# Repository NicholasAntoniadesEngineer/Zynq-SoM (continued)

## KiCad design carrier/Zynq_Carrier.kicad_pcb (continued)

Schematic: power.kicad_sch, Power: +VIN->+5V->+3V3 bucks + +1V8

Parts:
C20001, C20004, C20007, C20009, C20025, C20029: 100n; C_0603_1608Metric; LCSC C14663
C20002, C20003: 10u; C_1206_3216Metric; LCSC C13585
C20005, C20006, C20008, C20010, C20011, C20026, C20030: 22u; C_0805_2012Metric; LCSC C45783
C20012, C20013, C20024, C20028, C20031, C20032: 1u; C_0603_1608Metric; LCSC C15849
C20023, C20027: 22p; C_0603_1608Metric; LCSC C1653
D20001, D20002, D20003: red; LED_0603_1608Metric; LCSC C2286
L20001, L20002: 10uH; SWPA8040S100MT; LCSC C37429
Q20001: AO3400A; SOT-23; MPN AO3400A; LCSC C20917
R20001: 40.2k; R_0603_1608Metric; LCSC C12447
R20002, R20005: 10k; R_0603_1608Metric; LCSC C25804
R20003, R20007, R20012, R20015: 1k; R_0603_1608Metric; LCSC C21190
R20004: 23.2k; R_0603_1608Metric; LCSC C23346
R20006, R20009: 330R; R_0603_1608Metric; LCSC C23138
R20008: 100k; R_0603_1608Metric; LCSC C25803
R20010, R20014: 22k; R_0603_1608Metric; LCSC C31850
R20011, R20013: 10R; R_0603_1608Metric; LCSC C22859
TP20001: +5V; TestPoint_Pad_D1.5mm
TP20002: +3V3; TestPoint_Pad_D1.5mm
TP20003: +1V8; TestPoint_Pad_D1.5mm
TP20004: GND; TestPoint_Pad_D1.5mm
U20001, U20002: LM61460AANRJRR; LCSC C2864505
U20003: AP2112K-1.8; SOT-23-5; MPN AP2112K-1.8TRG1; LCSC C176944

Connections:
+1V8: R20007.1, TP20003.1; also elsewhere on the board
+1V8_REG: C20013.1, U20003.5 (VOUT); also elsewhere on the board
+3V3: C20012.1, D20003.2 (A), TP20002.1, U20003.1 (VIN); also elsewhere on the board
+3V3_REG: C20010.1, C20011.1, C20023.1, D20002.2 (A), L20002.2, R20004.1, R20013.1; also elsewhere on the board
+5V: C20007.1, C20008.1, C20029.1, C20030.1, TP20001.1, U20002.8 (VIN1), U20002.12 (VIN2); also elsewhere on the board
+5V_REG: C20005.1, C20006.1, C20026.1, C20027.1, D20001.2 (A), L20001.2, R20001.1, R20011.1; also elsewhere on the board
+VIN_SYS: C20001.1, C20002.1, C20003.1, C20025.1, U20001.8 (VIN1), U20001.12 (VIN2); also elsewhere on the board
/power/BIAS_3V3: C20032.1, R20013.2, U20002.1 (BIAS)
/power/BIAS_5V0: C20028.1, R20011.2, U20001.1 (BIAS)
/power/RT_3V3: R20014.1, U20002.6 (RT)
/power/RT_5V0: R20010.1, U20001.6 (RT)
EN_1V8: U20003.3 (EN); also elsewhere on the board
EN_3V3: U20002.7 (EN/SYNC); also elsewhere on the board
EN_5V0: U20001.7 (EN/SYNC); also elsewhere on the board
GND: C20001.2, C20002.2, C20003.2, C20005.2, C20006.2, C20007.2, C20008.2, C20010.2, C20011.2, C20012.2, C20013.2, C20024.2, C20025.2, C20026.2, C20028.2, C20029.2, C20030.2, C20031.2, C20032.2, Q20001.2 (S), R20002.2, R20003.2, R20005.2, R20006.2, R20008.2, R20010.2, R20014.2, TP20004.1, U20001.3 (AGND), U20001.9 (PGND1), U20001.11 (PGND2), U20002.3 (AGND), U20002.9 (PGND1), U20002.11 (PGND2), U20003.2 (GND); also elsewhere on the board
unnamed: C20023.2, R20015.1
unnamed: C20027.2, R20012.1
unnamed: D20001.1 (K), R20003.1
unnamed: D20002.1 (K), R20006.1
unnamed: D20003.1 (K), R20009.1
unnamed: Q20001.3 (D), R20009.2
unnamed: Q20001.1 (G), R20007.2, R20008.1
unnamed: C20004.1, U20001.13 (RBOOT), U20001.14 (CBOOT)
unnamed: R20001.2, R20002.1, R20012.2, U20001.4 (FB)
unnamed: C20004.2, L20001.1, U20001.10 (SW)
unnamed: C20024.1, U20001.2 (VCC)
unnamed: C20009.1, U20002.13 (RBOOT), U20002.14 (CBOOT)
unnamed: R20004.2, R20005.1, R20015.2, U20002.4 (FB)
unnamed: C20009.2, L20002.1, U20002.10 (SW)
unnamed: C20031.1, U20002.2 (VCC)

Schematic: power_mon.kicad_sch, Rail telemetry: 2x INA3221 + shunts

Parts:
C21001, C21002: 100n; C_0603_1608Metric; LCSC C14663
C21003: 10u; C_0805_2012Metric; LCSC C15850
R21001: 10k; R_0603_1608Metric; LCSC C25804
RS21001, RS21002, RS21003: 10mR; RLM12FTCMR010; LCSC C188070
RS21004: 20mR; RLM12FTCMR020; LCSC C393094
U21001, U21002: INA3221AIRGVR; LCSC C181255

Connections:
+1V8: RS21004.2, U21002.11 (IN-1); also elsewhere on the board
+1V8_REG: RS21004.1, U21002.12 (IN+1); also elsewhere on the board
+3V3: RS21003.2, U21001.1 (IN-3); also elsewhere on the board
+3V3_REG: RS21003.1, U21001.2 (IN+3); also elsewhere on the board
+3V3_SC: C21001.1, C21002.1, C21003.1, R21001.1, U21001.4 (VS), U21001.16 (VPU), U21002.4 (VS), U21002.5 (A0), U21002.16 (VPU); also elsewhere on the board
+5V: RS21002.2, U21001.14 (IN-2); also elsewhere on the board
+5V_REG: RS21002.1, U21001.15 (IN+2); also elsewhere on the board
+VIN: RS21001.1, U21001.12 (IN+1); also elsewhere on the board
+VIN_SYS: RS21001.2, U21001.11 (IN-1); also elsewhere on the board
GND: C21001.2, C21002.2, C21003.2, U21001.3 (GND), U21001.5 (A0), U21001.17 (PAD), U21002.1 (IN-3), U21002.2 (IN+3), U21002.3 (GND), U21002.14 (IN-2), U21002.15 (IN+2), U21002.17 (PAD); also elsewhere on the board
PMON_ALERT_N: R21001.2, U21001.9 (CRITICAL), U21002.9 (CRITICAL); also elsewhere on the board
STM32_I2C2_SCL: U21001.6 (SCL), U21002.6 (SCL); also elsewhere on the board
STM32_I2C2_SDA: U21001.7 (SDA), U21002.7 (SDA); also elsewhere on the board

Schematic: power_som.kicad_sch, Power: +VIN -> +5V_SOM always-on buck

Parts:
C22014, C22017, C22025: 100n; C_0603_1608Metric; LCSC C14663
C22015, C22016: 10u; C_1206_3216Metric; LCSC C13585
C22018, C22019: 22u; C_0805_2012Metric; LCSC C45783
C22021: 22p; C_0603_1608Metric; LCSC C1653
C22022, C22023: 1u; C_0603_1608Metric; LCSC C15849
D22004: red; LED_0603_1608Metric; LCSC C2286
L22003: 10uH; SWPA8040S100MT; LCSC C37429
R22014: 47.5k; R_0603_1608Metric; LCSC C23061
R22015: 13k; R_0603_1608Metric; LCSC C22797
R22016, R22019: 1k; R_0603_1608Metric; LCSC C21190
R22017: 10R; R_0603_1608Metric; LCSC C22859
R22018: 22k; R_0603_1608Metric; LCSC C31850
TP22001: +5V_SOM; TestPoint_Pad_D1.5mm
U22004: LM61460AANRJRR; LCSC C2864505

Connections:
+5V_SOM: C22018.1, C22019.1, C22021.1, D22004.2 (A), L22003.2, R22014.1, R22017.1, TP22001.1; also elsewhere on the board
+VIN_SYS: C22014.1, C22015.1, C22016.1, C22025.1, U22004.7 (EN/SYNC), U22004.8 (VIN1), U22004.12 (VIN2); also elsewhere on the board
/power_som/BIAS_5V_SOM: C22023.1, R22017.2, U22004.1 (BIAS)
/power_som/RT_5V_SOM: R22018.1, U22004.6 (RT)
GND: C22014.2, C22015.2, C22016.2, C22018.2, C22019.2, C22022.2, C22023.2, C22025.2, R22015.2, R22016.2, R22018.2, U22004.3 (AGND), U22004.9 (PGND1), U22004.11 (PGND2); also elsewhere on the board
unnamed: C22021.2, R22019.1
unnamed: D22004.1 (K), R22016.1
unnamed: C22017.1, U22004.13 (RBOOT), U22004.14 (CBOOT)
unnamed: R22014.2, R22015.1, R22019.2, U22004.4 (FB)
unnamed: C22017.2, L22003.1, U22004.10 (SW)
unnamed: C22022.1, U22004.2 (VCC)

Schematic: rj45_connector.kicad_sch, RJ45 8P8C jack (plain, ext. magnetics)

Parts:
J23001: KH-5224-8P8C-D; LCSC C2828085
R23001, R23002: 330R; R_0603_1608Metric; LCSC C23138

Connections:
+3V3: R23001.1, R23002.1; also elsewhere on the board
CHASSIS_GND: J23001.13 (SHELL); also elsewhere on the board
ETH_LINE_MDI_0_N: J23001.2; also elsewhere on the board
ETH_LINE_MDI_0_P: J23001.1; also elsewhere on the board
ETH_LINE_MDI_1_N: J23001.6; also elsewhere on the board
ETH_LINE_MDI_1_P: J23001.3; also elsewhere on the board
ETH_LINE_MDI_2_N: J23001.5; also elsewhere on the board
ETH_LINE_MDI_2_P: J23001.4; also elsewhere on the board
ETH_LINE_MDI_3_N: J23001.8; also elsewhere on the board
ETH_LINE_MDI_3_P: J23001.7; also elsewhere on the board
GND: J23001.10 (LED-L-), J23001.12 (LED-R-); also elsewhere on the board
unnamed: J23001.9 (LED-L+), R23001.2
unnamed: J23001.11 (LED-R+), R23002.2

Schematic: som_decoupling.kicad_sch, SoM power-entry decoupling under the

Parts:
C35001, C35002, C35007, C35008, C35013, C35014: 22u; C_0805_2012Metric; LCSC C45783
C35003, C35004, C35005, C35006, C35009, C35010, C35011, C35012, C35015, C35016, C35017, C35018: 100n; C_0603_1608Metric; LCSC C14663

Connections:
+3V3: C35007.1, C35008.1, C35009.1, C35010.1, C35011.1, C35012.1; also elsewhere on the board
+3V3_SC: C35013.1, C35014.1, C35015.1, C35016.1, C35017.1, C35018.1; also elsewhere on the board
+5V_SOM: C35001.1, C35002.1, C35003.1, C35004.1, C35005.1, C35006.1; also elsewhere on the board
GND: C35001.2, C35002.2, C35003.2, C35004.2, C35005.2, C35006.2, C35007.2, C35008.2, C35009.2, C35010.2, C35011.2, C35012.2, C35013.2, C35014.2, C35015.2, C35016.2, C35017.2, C35018.2; also elsewhere on the board

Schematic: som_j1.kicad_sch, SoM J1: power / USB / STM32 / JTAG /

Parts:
J24001: DF40C-100DP-0.4V(51); DF40C-100DP-0.4V_51; LCSC C531031

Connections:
+3V3_SC: J24001.37; also elsewhere on the board
+5V_SOM: J24001.1, J24001.2, J24001.3, J24001.4, J24001.5, J24001.6, J24001.7, J24001.8, J24001.9, J24001.10, J24001.11, J24001.12, J24001.13, J24001.14; also elsewhere on the board
ETH_LED1: J24001.98
ETH_LED2: J24001.94
ETH_PHY_MDI0_N: J24001.95; also elsewhere on the board
ETH_PHY_MDI0_P: J24001.97; also elsewhere on the board
ETH_PHY_MDI1_N: J24001.89; also elsewhere on the board
ETH_PHY_MDI1_P: J24001.91; also elsewhere on the board
ETH_PHY_MDI2_N: J24001.83; also elsewhere on the board
ETH_PHY_MDI2_P: J24001.85; also elsewhere on the board
ETH_PHY_MDI3_N: J24001.77; also elsewhere on the board
ETH_PHY_MDI3_P: J24001.79; also elsewhere on the board
FMC_LA08_N: J24001.92; also elsewhere on the board
FMC_LA08_P: J24001.74; also elsewhere on the board
FMC_LA09_N: J24001.84; also elsewhere on the board
FMC_LA09_P: J24001.80; also elsewhere on the board
FMC_LA10_N: J24001.88; also elsewhere on the board
FMC_LA10_P: J24001.90; also elsewhere on the board
FMC_LA11_N: J24001.76; also elsewhere on the board
FMC_LA11_P: J24001.78; also elsewhere on the board
GND: J24001.15, J24001.16, J24001.17, J24001.18, J24001.23, J24001.28, J24001.34, J24001.39, J24001.44, J24001.51, J24001.62, J24001.63, J24001.72, J24001.75, J24001.81, J24001.82, J24001.87, J24001.93, J24001.96, J24001.99; also elsewhere on the board
IO_0_35: J24001.86
IO_L2_N_35: J24001.100
SC_INT_N: J24001.41; also elsewhere on the board
SDIO_CLK: J24001.67; also elsewhere on the board
SDIO_CMD: J24001.69; also elsewhere on the board
SDIO_D0: J24001.65; also elsewhere on the board
SDIO_D1: J24001.61; also elsewhere on the board
SDIO_D2: J24001.73; also elsewhere on the board
SDIO_D3: J24001.71; also elsewhere on the board
STM32_BOOT0: J24001.57; also elsewhere on the board
STM32_GPIO5: J24001.53; also elsewhere on the board
STM32_GPIO6: J24001.45; also elsewhere on the board
STM32_GPIO7: J24001.59; also elsewhere on the board
STM32_GPIO8: J24001.54; also elsewhere on the board
STM32_I2C2_SCL: J24001.55; also elsewhere on the board
STM32_I2C2_SDA: J24001.49; also elsewhere on the board
STM32_NRST: J24001.47; also elsewhere on the board
STM32_RAIL_EN_1V8: J24001.43; also elsewhere on the board
STM32_RAIL_EN_3V3: J24001.35; also elsewhere on the board
STM32_RAIL_EN_5V0: J24001.33; also elsewhere on the board
STM32_USB_CC1: J24001.29; also elsewhere on the board
STM32_USB_CC2: J24001.31; also elsewhere on the board
STM32_USB_D_N: J24001.21; also elsewhere on the board
STM32_USB_D_P: J24001.19; also elsewhere on the board
USB_D+: J24001.32; also elsewhere on the board
USB_D-: J24001.30; also elsewhere on the board
USB_ID: J24001.20; also elsewhere on the board
USB_VBUS: J24001.22; also elsewhere on the board
VBUS_OUT_EN: J24001.38; also elsewhere on the board
ZYNQ_PS_MIO0: J24001.50
ZYNQ_PS_MIO7/VM0: J24001.40
ZYNQ_PS_MIO8\VM1: J24001.36
ZYNQ_PS_MIO9: J24001.52
ZYNQ_PS_MIO12: J24001.46
ZYNQ_PS_UART0_RXD: J24001.42; also elsewhere on the board
ZYNQ_PS_UART0_TXD: J24001.48; also elsewhere on the board
ZYNQ_TCK: J24001.64; also elsewhere on the board
ZYNQ_TDI: J24001.70; also elsewhere on the board
ZYNQ_TDO: J24001.68; also elsewhere on the board
ZYNQ_TMS: J24001.66; also elsewhere on the board

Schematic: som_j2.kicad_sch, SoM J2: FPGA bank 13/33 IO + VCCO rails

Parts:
J25002: DF40C-100DP-0.4V(51); DF40C-100DP-0.4V_51; LCSC C531031

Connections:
+3V3: J25002.1, J25002.2, J25002.3, J25002.98, J25002.99, J25002.100; also elsewhere on the board
DBG_UART_RXD: J25002.42; also elsewhere on the board
DBG_UART_TXD: J25002.40; also elsewhere on the board
ESC_BUF_OE_N: J25002.57; also elsewhere on the board
ESC_FAULT_N: J25002.37; also elsewhere on the board
ESC_PWM_IN0: J25002.81; also elsewhere on the board
ESC_PWM_IN1: J25002.83; also elsewhere on the board
ESC_PWM_IN2: J25002.93; also elsewhere on the board
ESC_PWM_IN3: J25002.91; also elsewhere on the board
GND: J25002.4, J25002.5, J25002.6, J25002.15, J25002.16, J25002.25, J25002.26, J25002.35, J25002.36, J25002.45, J25002.46, J25002.55, J25002.56, J25002.65, J25002.66, J25002.75, J25002.76, J25002.85, J25002.86, J25002.95, J25002.96, J25002.97; also elsewhere on the board
HDMI_RX_5V_DET: J25002.44; also elsewhere on the board
HDMI_RX_CEC: J25002.59; also elsewhere on the board
HDMI_RX_CLK_N: J25002.88; also elsewhere on the board
HDMI_RX_CLK_P: J25002.90; also elsewhere on the board
HDMI_RX_D0_N: J25002.94; also elsewhere on the board
HDMI_RX_D0_P: J25002.92; also elsewhere on the board
HDMI_RX_D1_N: J25002.84; also elsewhere on the board
HDMI_RX_D1_P: J25002.82; also elsewhere on the board
HDMI_RX_D2_N: J25002.80; also elsewhere on the board
HDMI_RX_D2_P: J25002.78; also elsewhere on the board
IO_25_13: J25002.23; also elsewhere on the board
IO_L2_N_13: J25002.14; also elsewhere on the board
IO_L2_P_13: J25002.20; also elsewhere on the board
IO_L3_N_13: J25002.43; also elsewhere on the board
IO_L3_P_13: J25002.18; also elsewhere on the board
IO_L4_N_13: J25002.63; also elsewhere on the board
IO_L4_P_13: J25002.61; also elsewhere on the board
IO_L5P_13: J25002.38; also elsewhere on the board
IO_L5_N_13: J25002.24; also elsewhere on the board
IO_L6_P_13: J25002.21; also elsewhere on the board
IO_L6_P_33: J25002.89
IO_L7_N_13: J25002.64; also elsewhere on the board
IO_L7_P_13: J25002.62; also elsewhere on the board
IO_L8_N_13: J25002.60; also elsewhere on the board
IO_L8_P_13: J25002.58; also elsewhere on the board
IO_L9_DQS_N_13: J25002.48; also elsewhere on the board
IO_L9_DQS_P_13: J25002.50; also elsewhere on the board
IO_L10_N_13: J25002.51; also elsewhere on the board
IO_L10_P_13: J25002.53; also elsewhere on the board
IO_L15_P_13: J25002.9; also elsewhere on the board
IO_L19_P_13: J25002.12; also elsewhere on the board
IO_L21_P_13: J25002.13; also elsewhere on the board
IO_L22_P_13: J25002.19; also elsewhere on the board
IO_L24_N_13: J25002.7; also elsewhere on the board
IO_L24_P_13: J25002.10; also elsewhere on the board
LCD_CTP_INT: J25002.32; also elsewhere on the board
LCD_CTP_RST: J25002.34; also elsewhere on the board
LCD_CTP_SCL: J25002.28; also elsewhere on the board
LCD_CTP_SDA: J25002.30; also elsewhere on the board
PL_BTN0: J25002.79; also elsewhere on the board
PL_BTN1: J25002.87; also elsewhere on the board
PMODX_IO1: J25002.29; also elsewhere on the board
PMODX_IO2: J25002.27; also elsewhere on the board
PMODX_IO3: J25002.33; also elsewhere on the board
PMODX_IO4: J25002.31; also elsewhere on the board
PMODX_IO5: J25002.41; also elsewhere on the board
PMODX_IO6: J25002.39; also elsewhere on the board
PMODX_IO7: J25002.49; also elsewhere on the board
PMODX_IO8: J25002.47; also elsewhere on the board
SD_CARD_DETECT: J25002.17; also elsewhere on the board
ZYNQ_HDMI_TX_CEC: J25002.77; also elsewhere on the board
ZYNQ_HDMI_TX_HPD: J25002.54; also elsewhere on the board
ZYNQ_HDMI_TX_SCL: J25002.22; also elsewhere on the board
ZYNQ_HDMI_TX_SDA: J25002.52; also elsewhere on the board
ZYNQ_HDMI_TX_TMDS_0_N: J25002.69; also elsewhere on the board
ZYNQ_HDMI_TX_TMDS_0_P: J25002.67; also elsewhere on the board
ZYNQ_HDMI_TX_TMDS_1_N: J25002.68; also elsewhere on the board
ZYNQ_HDMI_TX_TMDS_1_P: J25002.70; also elsewhere on the board
ZYNQ_HDMI_TX_TMDS_2_N: J25002.74; also elsewhere on the board
ZYNQ_HDMI_TX_TMDS_2_P: J25002.72; also elsewhere on the board
ZYNQ_HDMI_TX_TMDS_CLK_N: J25002.73; also elsewhere on the board
ZYNQ_HDMI_TX_TMDS_CLK_P: J25002.71; also elsewhere on the board
ZYNQ_PS_UART0_CTS_N: J25002.11; also elsewhere on the board
ZYNQ_PS_UART0_RTS_N: J25002.8; also elsewhere on the board

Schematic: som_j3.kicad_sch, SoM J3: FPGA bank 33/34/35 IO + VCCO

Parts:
J26003: DF40C-100DP-0.4V(51); DF40C-100DP-0.4V_51; LCSC C531031

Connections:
+2V5_VADJ: J26003.1, J26003.2, J26003.4; also elsewhere on the board
+3V3: J26003.97, J26003.99; also elsewhere on the board
CAM_CLK_N: J26003.11; also elsewhere on the board
CAM_CLK_P: J26003.9; also elsewhere on the board
CAM_D0_N: J26003.7; also elsewhere on the board
CAM_D0_P: J26003.5; also elsewhere on the board
CAM_D1_N: J26003.15; also elsewhere on the board
CAM_D1_P: J26003.17; also elsewhere on the board
CAM_EN: J26003.85; also elsewhere on the board
CAM_LED: J26003.87; also elsewhere on the board
CAM_SCL: J26003.86; also elsewhere on the board
CAM_SDA: J26003.89; also elsewhere on the board
ESC_PWM_IN4: J26003.91; also elsewhere on the board
ESC_PWM_IN5: J26003.93; also elsewhere on the board
ESC_PWM_IN6: J26003.92; also elsewhere on the board
ESC_PWM_IN7: J26003.94; also elsewhere on the board
FMC_CLK0_M2C_N: J26003.16; also elsewhere on the board
FMC_CLK0_M2C_P: J26003.14; also elsewhere on the board
FMC_CLK1_M2C_N: J26003.10; also elsewhere on the board
FMC_CLK1_M2C_P: J26003.8; also elsewhere on the board
FMC_LA00_CC_N: J26003.20; also elsewhere on the board
FMC_LA00_CC_P: J26003.22; also elsewhere on the board
FMC_LA01_CC_N: J26003.26; also elsewhere on the board
FMC_LA01_CC_P: J26003.24; also elsewhere on the board
FMC_LA02_N: J26003.35; also elsewhere on the board
FMC_LA02_P: J26003.37; also elsewhere on the board
FMC_LA03_N: J26003.32; also elsewhere on the board
FMC_LA03_P: J26003.34; also elsewhere on the board
FMC_LA04_N: J26003.44; also elsewhere on the board
FMC_LA04_P: J26003.42; also elsewhere on the board
FMC_LA05_N: J26003.45; also elsewhere on the board
FMC_LA05_P: J26003.47; also elsewhere on the board
FMC_LA06_N: J26003.49; also elsewhere on the board
FMC_LA06_P: J26003.51; also elsewhere on the board
FMC_LA07_N: J26003.52; also elsewhere on the board
FMC_LA07_P: J26003.50; also elsewhere on the board
GND: J26003.3, J26003.6, J26003.12, J26003.13, J26003.18, J26003.23, J26003.28, J26003.33, J26003.38, J26003.43, J26003.48, J26003.53, J26003.58, J26003.63, J26003.68, J26003.73, J26003.80, J26003.83, J26003.90, J26003.95, J26003.100; also elsewhere on the board
IO_L16_N_35: J26003.29
IO_L16_P_35: J26003.31
IO_L18_N_35: J26003.25
IO_L18_P_35: J26003.27
IO_L22_N_34: J26003.84
IO_L23_P_34: J26003.88
IO_L24_P_34: J26003.82
LCD_B0: J26003.65; also elsewhere on the board
LCD_B1: J26003.66; also elsewhere on the board
LCD_B2: J26003.67; also elsewhere on the board
LCD_B3: J26003.69; also elsewhere on the board
LCD_B4: J26003.70; also elsewhere on the board
LCD_B5: J26003.71; also elsewhere on the board
LCD_B6: J26003.72; also elsewhere on the board
LCD_B7: J26003.74; also elsewhere on the board
LCD_BL_PWM: J26003.81; also elsewhere on the board
LCD_DE: J26003.78; also elsewhere on the board
LCD_DISP: J26003.79; also elsewhere on the board
LCD_G0: J26003.55; also elsewhere on the board
LCD_G1: J26003.56; also elsewhere on the board
LCD_G2: J26003.57; also elsewhere on the board
LCD_G3: J26003.59; also elsewhere on the board
LCD_G4: J26003.60; also elsewhere on the board
LCD_G5: J26003.61; also elsewhere on the board
LCD_G6: J26003.62; also elsewhere on the board
LCD_G7: J26003.64; also elsewhere on the board
LCD_HSYNC: J26003.76; also elsewhere on the board
LCD_PCLK: J26003.75; also elsewhere on the board
LCD_R0: J26003.19; also elsewhere on the board
LCD_R1: J26003.21; also elsewhere on the board
LCD_R2: J26003.30; also elsewhere on the board
LCD_R3: J26003.36; also elsewhere on the board
LCD_R4: J26003.40; also elsewhere on the board
LCD_R5: J26003.41; also elsewhere on the board
LCD_R6: J26003.46; also elsewhere on the board
LCD_R7: J26003.54; also elsewhere on the board
LCD_VSYNC: J26003.77; also elsewhere on the board
PUDC_34: J26003.39; also elsewhere on the board
WATCHDOG_KICK: J26003.96; also elsewhere on the board
WATCHDOG_RST_N: J26003.98; also elsewhere on the board

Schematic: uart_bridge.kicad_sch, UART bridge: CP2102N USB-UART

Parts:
C27001, C27003, C27004: 100n; C_0603_1608Metric; LCSC C14663
C27002: 10u; C_0805_2012Metric; LCSC C15850
R27001: 1k; R_0603_1608Metric; LCSC C21190
R27002: 22k1; R_0603_1608Metric; LCSC C25961
R27003: 47k5; R_0603_1608Metric; LCSC C23061
TP27001: ZYNQ_PS_UART0_TXD; TestPoint_Pad_D1.5mm
TP27002: ZYNQ_PS_UART0_RXD; TestPoint_Pad_D1.5mm
U27001: CP2102N-A02; CP2102N-A02-GQFN24R; LCSC C969151

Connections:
+3V3: C27001.1, C27002.1, C27003.1, C27004.1, R27001.1, U27001.5 (VIO), U27001.6 (VDD), U27001.7 (VREGIN); also elsewhere on the board
/uart_bridge/CP2102N_VBUS_SNS: R27002.2, R27003.1, U27001.8 (VBUS)
GND: C27001.2, C27002.2, C27003.2, C27004.2, R27003.2, U27001.2 (GND), U27001.25 (GND); also elsewhere on the board
unnamed: R27001.2, U27001.9 (RSTb)
USB_UART_DM: U27001.4 (D-); also elsewhere on the board
USB_UART_DP: U27001.3 (D+); also elsewhere on the board
USB_UART_VBUS: R27002.1; also elsewhere on the board
ZYNQ_PS_UART0_CTS_N: U27001.19 (RTS); also elsewhere on the board
ZYNQ_PS_UART0_RTS_N: U27001.18 (CTS); also elsewhere on the board
ZYNQ_PS_UART0_RXD: TP27002.1, U27001.21 (TXD); also elsewhere on the board
ZYNQ_PS_UART0_TXD: TP27001.1, U27001.20 (RXD); also elsewhere on the board

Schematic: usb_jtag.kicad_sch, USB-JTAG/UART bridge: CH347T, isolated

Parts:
C28001: 1u; C_0603_1608Metric; LCSC C15849
C28002: 10u; C_0805_2012Metric; LCSC C15850
C28003, C28004, C28007: 100n; C_0603_1608Metric; LCSC C14663
C28005, C28006: 16p; C_0603_1608Metric; LCSC C162205
R28001, R28002, R28003: 10k; R_0603_1608Metric; LCSC C25804
R28004: 100k; R_0603_1608Metric; LCSC C25803
SW28001: DSHP04TSGER; LCSC C3293144
TP28001: +3V3_DBG; TestPoint_Pad_D1.5mm
TP28002: DBG_UART_TXD; TestPoint_Pad_D1.5mm
TP28003: DBG_UART_RXD; TestPoint_Pad_D1.5mm
U28001: CH347T; LCSC C5122332
U28002: SN74LVC125ADR; LCSC C7661
U28004: AP2112K-3.3TRG1; LCSC C51118
Y28001: 8MHz; 1C208000BC0R; LCSC C57131

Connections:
+3V3_DBG: C28002.1, C28003.1, C28004.1, C28007.1, R28001.1, R28004.1, TP28001.1, U28001.14 (VCC), U28002.14 (VCC), U28004.5 (VOUT)
+5V_DBG: C28001.1, U28004.1 (VIN), U28004.3 (EN); also elsewhere on the board
/usb_jtag/DBG_FT_TCK: U28001.6 (CTS0/GPIO0/SCK/TCK), U28002.2 (1A)
/usb_jtag/DBG_FT_TDI: U28001.8 (TXD0/MOSI/TDI), U28002.5 (2A)
/usb_jtag/DBG_FT_TDO: U28001.7 (RTS0/GPIO1/MISO/TDO), U28002.8 (3Y)
/usb_jtag/DBG_FT_TMS: U28001.5 (DSR0/GPIO2/SCS0/TMS), U28002.12 (4A)
/usb_jtag/DBG_JTAG_OE_N: R28004.2, SW28001.1, U28002.1 (1OE#), U28002.4 (2OE#), U28002.10 (3OE#), U28002.13 (4OE#)
/usb_jtag/DBG_XI: C28005.1, U28001.19 (XI), Y28001.1 (OSC1)
/usb_jtag/DBG_XO: C28006.1, U28001.20 (XO), Y28001.3 (OSC2)
DBG_UART_RXD: TP28003.1, U28001.3 (TXD1); also elsewhere on the board
DBG_UART_TXD: TP28002.1, U28001.4 (RXD1); also elsewhere on the board
DBG_USB_DM: U28001.16 (UD-); also elsewhere on the board
DBG_USB_DP: U28001.17 (UD+); also elsewhere on the board
GND: C28001.2, C28002.2, C28003.2, C28004.2, C28005.2, C28006.2, C28007.2, R28002.2, R28003.2, SW28001.8, U28001.18 (GND), U28002.7 (GND), U28004.2 (GND), Y28001.2 (NC), Y28001.4 (NC); also elsewhere on the board
unnamed: R28001.2, U28001.1 (RST#)
unnamed: R28003.1, U28001.13 (RTS1/GPIO7)
unnamed: R28002.1, U28001.10 (TNOW1/DTR1)
ZYNQ_TCK: U28002.3 (1Y); also elsewhere on the board
ZYNQ_TDI: U28002.6 (2Y); also elsewhere on the board
ZYNQ_TDO: U28002.9 (3A); also elsewhere on the board
ZYNQ_TMS: U28002.11 (4Y); also elsewhere on the board

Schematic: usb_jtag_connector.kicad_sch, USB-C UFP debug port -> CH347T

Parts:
C29001: 10u; C_0805_2012Metric; LCSC C15850
J29001: TYPE-C-31-M-12; LCSC C165948
R29001, R29002: 5.1k; R_0603_1608Metric; LCSC C23186
TP29001: +5V_DBG; TestPoint_Pad_D1.5mm
U29001: USBLC6-2SC6; LCSC C7519

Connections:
+5V_DBG: C29001.1, J29001.A4B9 (VBUS), J29001.B4A9 (VBUS), TP29001.1, U29001.5; also elsewhere on the board
/usb_jtag_connector/DBG_USB_DM_CONN: J29001.A7 (DN1), J29001.B7 (DN2), U29001.3
/usb_jtag_connector/DBG_USB_DP_CONN: J29001.A6 (DP1), J29001.B6 (DP2), U29001.1
CHASSIS_GND: J29001.1 (EH), J29001.2 (EH), J29001.3 (EH), J29001.4 (EH); also elsewhere on the board
DBG_USB_DM: U29001.4; also elsewhere on the board
DBG_USB_DP: U29001.6; also elsewhere on the board
GND: C29001.2, J29001.A1B12 (GND), J29001.B1A12 (GND), R29001.2, R29002.2, U29001.2; also elsewhere on the board
unnamed: J29001.A5 (CC1), R29001.1
unnamed: J29001.B5 (CC2), R29002.1

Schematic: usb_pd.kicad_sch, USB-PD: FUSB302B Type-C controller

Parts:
C30001, C30003: 100n; C_0603_1608Metric; LCSC C14663
C30002: 10u; C_0805_2012Metric; LCSC C15850
C30004, C30005: 200p; C_0603_1608Metric; LCSC C113796
U30001: FUSB302BMPX; WQFN-14-1EP_2.5x2.5mm_P0.5mm_EP1.45x1.45mm; MPN FUSB302BMPX; LCSC C132291

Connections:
+3V3_SC: C30001.1, C30002.1, U30001.3 (VDD), U30001.4 (VDD); also elsewhere on the board
+VBUS_IN: C30003.1, U30001.2 (VBUS); also elsewhere on the board
GND: C30001.2, C30002.2, C30003.2, C30004.2, C30005.2, U30001.8 (GND), U30001.9 (GND), U30001.15 (GND); also elsewhere on the board
SC_INT_N: U30001.5 (INT_N); also elsewhere on the board
STM32_I2C2_SCL: U30001.6 (SCL); also elsewhere on the board
STM32_I2C2_SDA: U30001.7 (SDA); also elsewhere on the board
STM32_USB_CC1: C30004.1, U30001.10 (CC1), U30001.11 (CC1); also elsewhere on the board
STM32_USB_CC2: C30005.1, U30001.1 (CC2), U30001.14 (CC2); also elsewhere on the board

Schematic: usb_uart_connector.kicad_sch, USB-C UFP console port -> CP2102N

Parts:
C31001: 10u; C_0805_2012Metric; LCSC C15850
J31001: TYPE-C-31-M-12; LCSC C165948
R31001, R31002: 5.1k; R_0603_1608Metric; LCSC C23186
U31001: USBLC6-2SC6; LCSC C7519

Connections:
/usb_uart_connector/USB_UART_DM_CONN: J31001.A7 (DN1), J31001.B7 (DN2), U31001.3
/usb_uart_connector/USB_UART_DP_CONN: J31001.A6 (DP1), J31001.B6 (DP2), U31001.1
CHASSIS_GND: J31001.1 (EH), J31001.2 (EH), J31001.3 (EH), J31001.4 (EH); also elsewhere on the board
GND: C31001.2, J31001.A1B12 (GND), J31001.B1A12 (GND), R31001.2, R31002.2, U31001.2; also elsewhere on the board
unnamed: J31001.A5 (CC1), R31001.1
unnamed: J31001.B5 (CC2), R31002.1
USB_UART_DM: U31001.4; also elsewhere on the board
USB_UART_DP: U31001.6; also elsewhere on the board
USB_UART_VBUS: C31001.1, J31001.A4B9 (VBUS), J31001.B4A9 (VBUS), U31001.5; also elsewhere on the board

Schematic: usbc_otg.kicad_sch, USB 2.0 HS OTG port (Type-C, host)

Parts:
C32001: 100n; C_0603_1608Metric; LCSC C14663
C32002: 22u; C_0805_2012Metric; LCSC C45783
C32003: 100u; RVT1C101M0605_100UF_16V; LCSC C970684
J32002: TYPE-C-31-M-12; LCSC C165948
R32001, R32002: 56k; R_0603_1608Metric; LCSC C23206
R32003, R32005: 100k; R_0603_1608Metric; LCSC C25803
R32004: 1k; R_0603_1608Metric; LCSC C21190
TP32001: VBUS_OUT_EN; TestPoint_Pad_D1.5mm
U32001: TPS2051CDBVR; LCSC C129581
U32002: USBLC6-2SC6; LCSC C7519

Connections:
+3V3_SC: R32003.1; also elsewhere on the board
+5V_USB: C32001.1, U32001.5 (IN); also elsewhere on the board
/usbc_otg/USBC_DM_CONN: J32002.A7 (DN1), J32002.B7 (DN2), U32002.3
/usbc_otg/USBC_DP_CONN: J32002.A6 (DP1), J32002.B6 (DP2), U32002.1
CHASSIS_GND: J32002.1 (EH), J32002.2 (EH), J32002.3 (EH), J32002.4 (EH); also elsewhere on the board
GND: C32001.2, C32002.2, C32003.2, J32002.A1B12 (GND), J32002.B1A12 (GND), R32004.2, R32005.2, U32001.2 (GND), U32002.2; also elsewhere on the board
unnamed: J32002.A5 (CC1), R32001.2
unnamed: J32002.B5 (CC2), R32002.2
USBOTG_FLT_N: R32003.2, U32001.3 (FLT#); also elsewhere on the board
USB_D+: U32002.6; also elsewhere on the board
USB_D-: U32002.4; also elsewhere on the board
USB_ID: R32004.1; also elsewhere on the board
USB_VBUS: C32002.1, C32003.1, J32002.A4B9 (VBUS), J32002.B4A9 (VBUS), R32001.1, R32002.1, U32001.1 (OUT), U32002.5; also elsewhere on the board
VBUS_OUT_EN: R32005.1, TP32001.1, U32001.4 (EN(EN#)); also elsewhere on the board

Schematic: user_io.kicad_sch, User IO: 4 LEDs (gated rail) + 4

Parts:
C33001: 100n; C_0603_1608Metric; LCSC C14663
D33001: red; LED_0603_1608Metric; LCSC C2286
D33002: green; LED_0603_1608Metric; LCSC C12624
D33003: blue; LED_0603_1608Metric; LCSC C2288
D33004: white; LED_0603_1608Metric; LCSC C2290
R33001: 1k; R_0603_1608Metric; LCSC C21190
R33002, R33003, R33004: 200R; R_0603_1608Metric; LCSC C8218
R33005, R33006, R33007, R33008: 10k; R_0603_1608Metric; LCSC C25804
SW33001, SW33002, SW33003, SW33004: USER; TS-1187A-B-A-B; LCSC C318884

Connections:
+3V3: R33005.1, R33006.1, R33007.1, R33008.1; also elsewhere on the board
+3V3_USER_LED: C33001.1, D33001.2 (A), D33002.2 (A), D33003.2 (A), D33004.2 (A); also elsewhere on the board
GND: C33001.2, SW33001.3 (C), SW33001.4 (D), SW33002.3 (C), SW33002.4 (D), SW33003.3 (C), SW33003.4 (D), SW33004.3 (C), SW33004.4 (D); also elsewhere on the board
IO_25_13: R33001.2; also elsewhere on the board
IO_L6_P_13: R33002.2; also elsewhere on the board
IO_L15_P_13: R33005.2, SW33001.1 (A), SW33001.2 (B); also elsewhere on the board
IO_L19_P_13: R33006.2, SW33002.1 (A), SW33002.2 (B); also elsewhere on the board
IO_L21_P_13: R33007.2, SW33003.1 (A), SW33003.2 (B); also elsewhere on the board
IO_L22_P_13: R33008.2, SW33004.1 (A), SW33004.2 (B); also elsewhere on the board
IO_L24_N_13: R33004.2; also elsewhere on the board
IO_L24_P_13: R33003.2; also elsewhere on the board
unnamed: D33001.1 (K), R33001.1
unnamed: D33002.1 (K), R33002.1
unnamed: D33003.1 (K), R33003.1
unnamed: D33004.1 (K), R33004.1

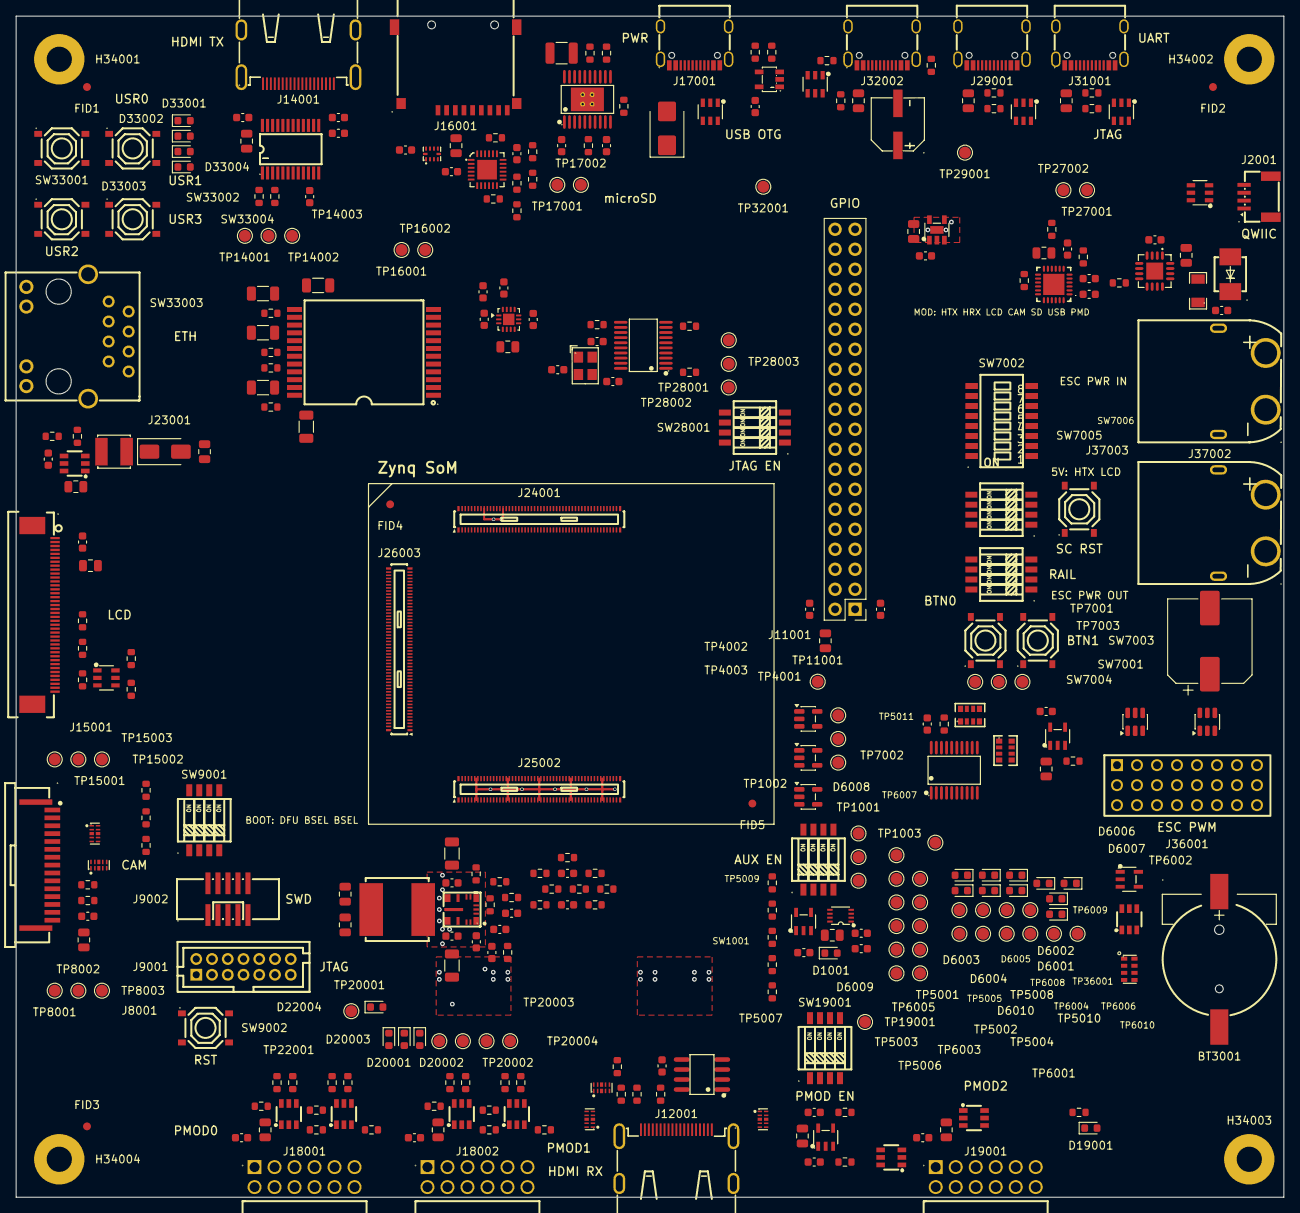
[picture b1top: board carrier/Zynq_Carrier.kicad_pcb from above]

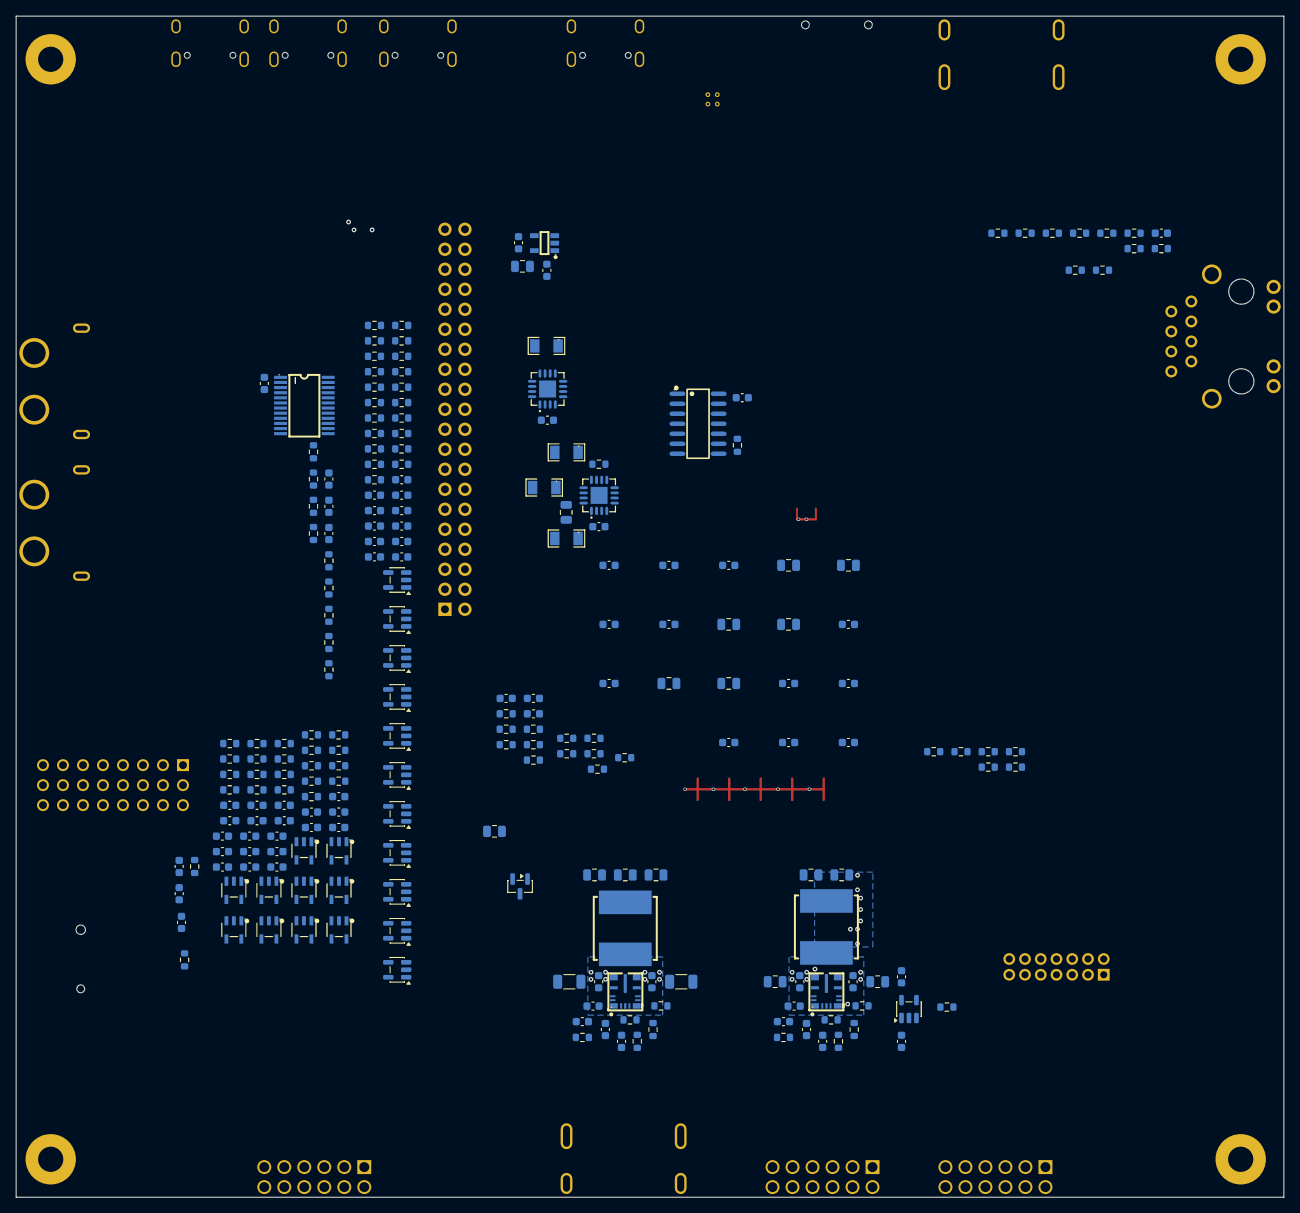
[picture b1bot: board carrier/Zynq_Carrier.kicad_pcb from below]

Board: 4 copper layers, 161.0 x 150.0 mm, 566 parts (221 on the bottom side), 434 nets.

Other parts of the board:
FID1, FID2, FID3, FID4, FID5: Fiducial; Fiducial_1mm_Mask2mm
